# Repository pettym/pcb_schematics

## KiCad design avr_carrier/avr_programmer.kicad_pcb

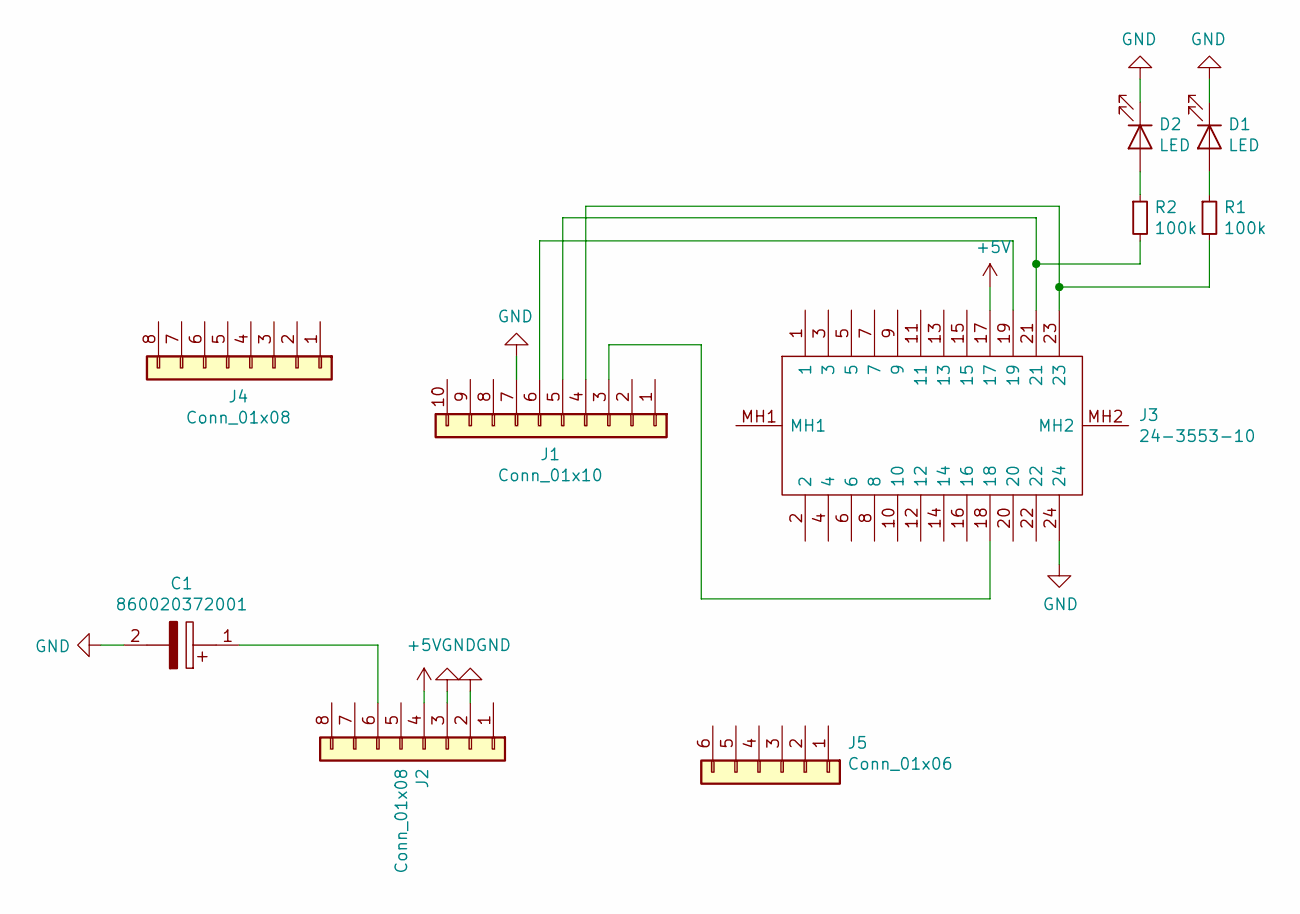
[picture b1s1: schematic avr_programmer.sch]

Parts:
C1: 860020372001; CAPPRD200W52D500H1250; Mouser Part Number 710-860020372001
D1, D2: LED; LTL4232
J1: Conn_01x10; PinHeader_1x10_P2.54mm_Vertical
J2, J4: Conn_01x08; PinHeader_1x08_P2.54mm_Vertical
J3: 24-3553-10; 24355310; Mouser Part Number 535-24-3553-10
J5: Conn_01x06; PinHeader_1x06_P2.54mm_Vertical
R1, R2: 100k; RESAD1100W50L340D190

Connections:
+5V: J2.4, J3.17
GND: C1.2, D1.1 (K), D2.1 (K), J1.7, J2.2, J2.3, J3.24
unnamed: C1.1, J2.6
unnamed: D1.2 (A), R1.1
unnamed: D2.2 (A), R2.1
unnamed: J1.3, J3.18
unnamed: J1.4, J3.23, R1.2
unnamed: J1.5, J3.21, R2.2
unnamed: J1.6, J3.19

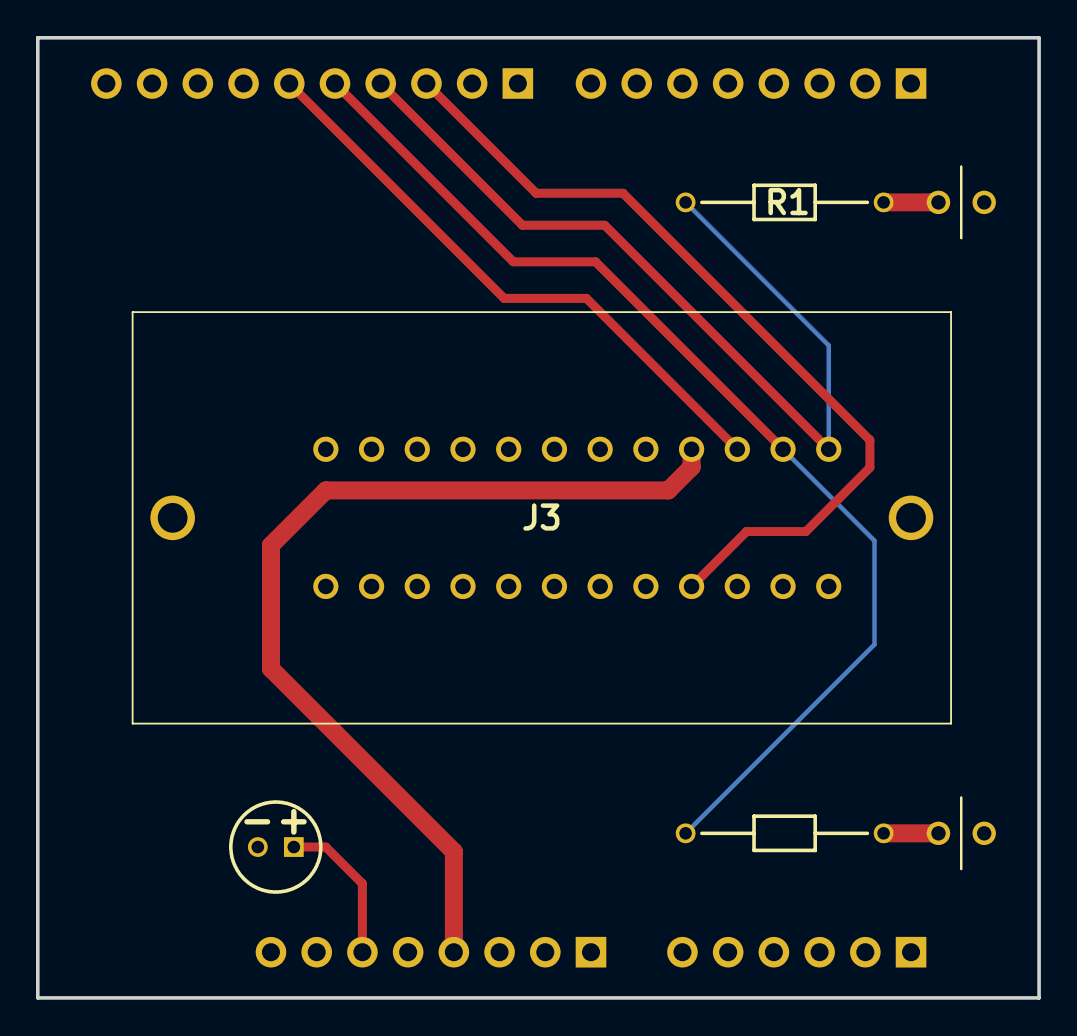
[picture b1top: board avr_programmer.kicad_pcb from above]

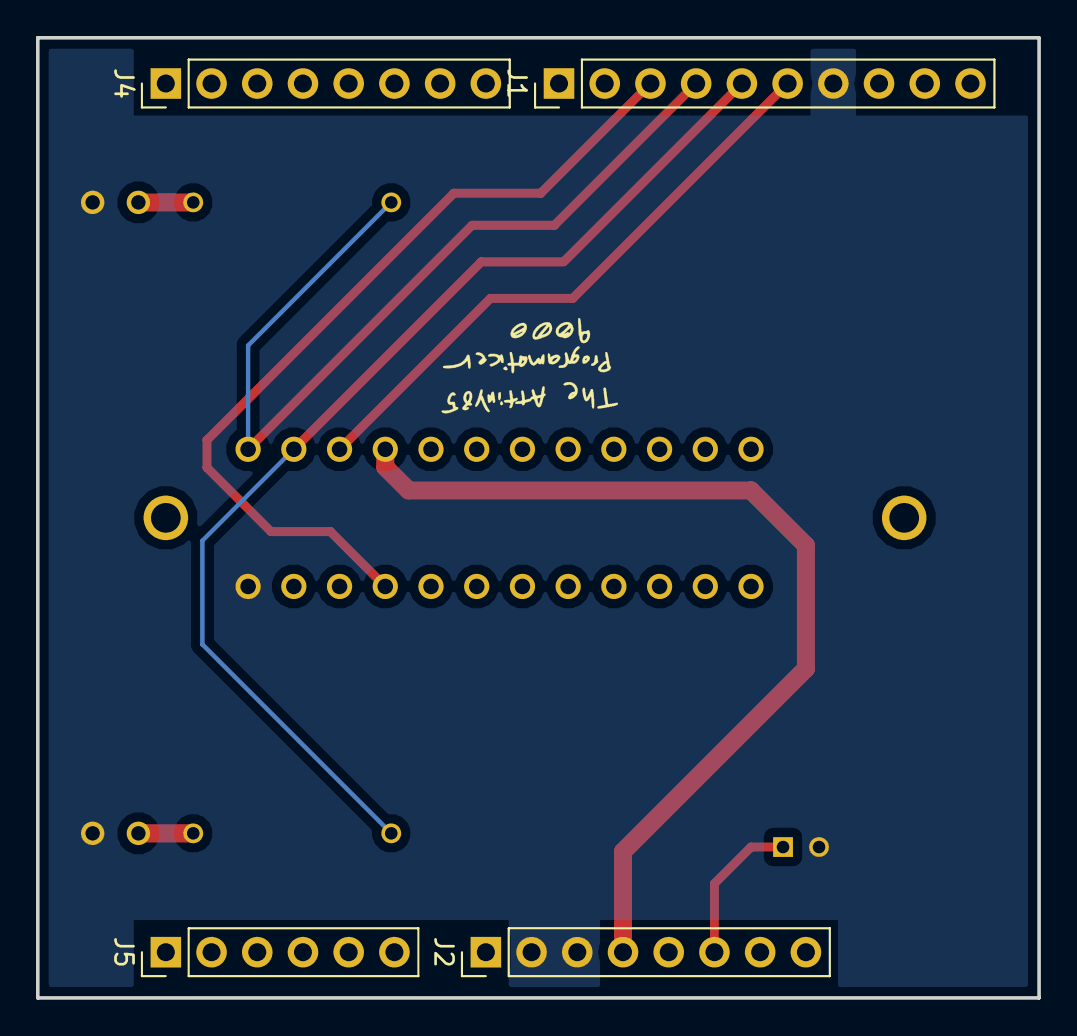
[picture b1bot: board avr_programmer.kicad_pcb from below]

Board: 2 copper layers, 55.6 x 53.3 mm, 10 parts (4 on the bottom side), 9 nets.

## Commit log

2022-08-04 init
